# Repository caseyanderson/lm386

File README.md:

# LM386
Casey Anderson, 2018

## Overview

This repository provides a `Printed Circuit Board` (`PCB`) file and BOM for a 1-watt DC Audio Amplifier (`LM386N-4`)

## PCB

This double-sided `Pin Through Hole` (`PTH`) PCB was created in EAGLE

### BOM

Note: items without a `Manufacturer Part Number` are generic

* 1x LM386N-4
* 1x SWITCH SLIDE SPDT 200MA 30V, `EG1218`
* 1x CONN PWR JACK 2X5.5MM SOLDER, `PJ-102A`
* 2x CONN JACK STEREO 3.5MM, `SJ1-3523N`
* 1x POT 10kR 1/20W CARBON LOG, `PTV09A-4020F-A103`
* 1x 330R
* 1x 1000uF (Electrolytic)
* 2x 100uF (Electrolytic)
* 1x 10uF (Electrolytic)
* 1x 0.1uF (Ceramic)
* 1x 5mm LED

### Photo

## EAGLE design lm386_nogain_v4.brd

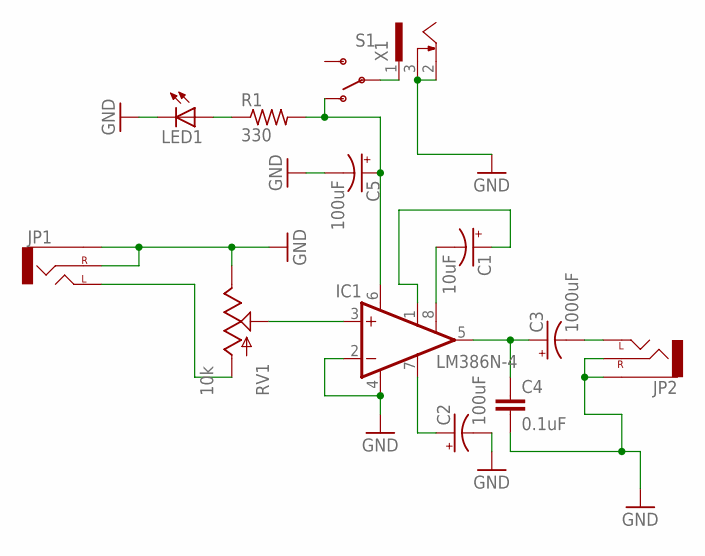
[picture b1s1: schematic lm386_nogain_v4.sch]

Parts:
C1: 10uF; CPOL-RADIAL-10UF-25V
C2: 100uF; CPOL-RADIAL-10UF-25V
C3: 1000uF; CPOL-RADIAL-10UF-25V
C4: 0.1uF; CAP-PTH-SMALL2
C5: 100uF; CPOL-RADIAL-100UF-25V
IC1: LM386N-4; DIL08
JP1, JP2: AUDIO-JACKPTH; AUDIO-JACK
LED1: LED5MM
R1: 330; 0204V
RV1: 10k; ALPS_POT
S1: SWITCH-SPDTPTH_LOCK; SWITCH-SPDT_LOCK.007S
X1: SCD-014A; SCD-014-A

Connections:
GND: C2.2 (-), C4.2, C5.2 (-), IC1.2 (-IN), IC1.4 (GND), JP1.RING (RIGHT), JP1.SLEEVE, JP2.RING (RIGHT), JP2.SLEEVE, LED1.K (C), RV1.P$1 (E), X1.2, X1.3
unnamed: JP1.TIP (LEFT), RV1.P$3 (A)
unnamed: IC1.3 (+IN), RV1.P$2 (S)
unnamed: S1.2, X1.1
unnamed: C5.1 (+), IC1.6 (VS), R1.2, S1.1 (O)
unnamed: C1.1 (+), IC1.1 (GAIN)
unnamed: C1.2 (-), IC1.8 (GAIN)
unnamed: C2.1 (+), IC1.7 (BYPASS)
unnamed: C3.1 (+), C4.1, IC1.5 (OUT)
unnamed: LED1.A, R1.1
unnamed: C3.2 (-), JP2.TIP (LEFT)

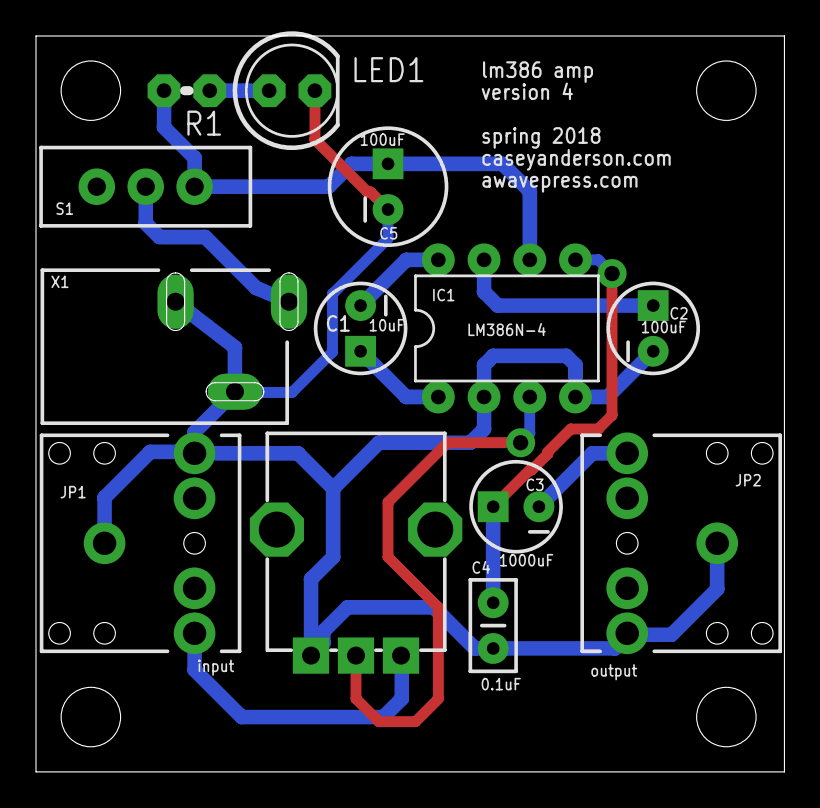
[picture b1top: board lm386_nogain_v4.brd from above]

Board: 2 copper layers, 41.6 x 40.9 mm, 17 parts (0 on the bottom side), 11 nets.

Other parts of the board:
U$1, U$2, U$3, U$4: STAND-OFF

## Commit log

2019-01-18 putting .brd and .sch in this repo
2019-09-08 adds .gitignore, README, and a photo of the pcb
2019-09-08 removing unnecessary periods

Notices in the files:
parts and their libraries:
SparkFun-Passives: Licensing: Creative Commons ShareAlike 4.0 International - https://creativecommons.org/licenses/by-sa/4.0
